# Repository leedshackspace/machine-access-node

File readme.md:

# Machine Node (WiFi)

Hardware and firmware to provide restricted access to dangerous and delicate
tools. Built around an ESP8266 (WeMos D1 mini) and RFID-RC522 breakout.

Designed to be easy to build for all levels of experience - simply order the PCB
from DirtyPCBs or OSHPark and solder the through hole parts to the board.
Software builds through the Arduino environment and will flash directly to the
WeMos board over USB.

## Hardware

To build a machine node you simply need to acquire a PCB - gerbers are available
in the hardware folder - and order the parts listed in the BOM.

[Schematic](hardware/images/schematic-rev1.png).

### Power Supply Options

There are three power supply options.

* **12 V DC Power**  
  This is the recommended option. Populate the 12 V DC section of the schematic, and also `C4` if you wish.
* **5 V DC Power** (Untested)  
  Populate the 12 V DC section of the schematic, and do not fit `U2` or `D2`. Use a jumper wire to bridge `D2` and connect the solder jumper `JP1`.  
  There is no polarity protection in this configuration.
* **240 AC Mains Power** (Untested)  
  Populate the 240 V AC section of the schematic. There is a PTC fuse inside the AC-DC power supply `U3` but there should be external fusing as well to protect small gauge cabling coming into the terminals.

### Relay Contacts

The relay is rated for 250 V, 6 A max. If you are switching heavy loads it is recommended that you use this to trip an external contactor.

### Latch Mode

The default state is "Present" mode, that is, the output will turn on when the card
is present and it will turn off when it is removed. An as yet untested mode allows the
node to read a card once and then keep the output enabled until an external signal is
received.

Feel free to test this mode out, you can modify settings in `settings.h`. Remember to include a button to allow the user to cancel their session.

### Faceplate

Enclosure parts are for laser cutting and will fit a [deep surface mount
pattress box](https://www.screwfix.com/p/lap-1-gang-surface-pattress-box-w-cable-clamp-earth-terminal-white-46mm/28489) available from LAP. You need to countersink the "solid" back plate
and fit screws through into the backbox compartment to secure the PCB in place.
Nylon screws & nuts are recommended to secure the PCB to minimize any interference
with the RFID signal. Typical metal faceplate screws are acceptable to attach
the faceplate to the backbox.

## Software

### Library Requirements
* [MFRC522 RFID](https://github.com/miguelbalboa/rfid)
* [ArduinoJson](https://arduinojson.org/)
* [ESP8266RestClient](https://github.com/fabianofranca/ESP8266RestClient)

Modify `settings-example.h` and rename as `settings.h`.

Requires the [Tool API server](https://github.com/leedshackspace/tool-api) running somewhere accessible, at least until the cards have been cached.

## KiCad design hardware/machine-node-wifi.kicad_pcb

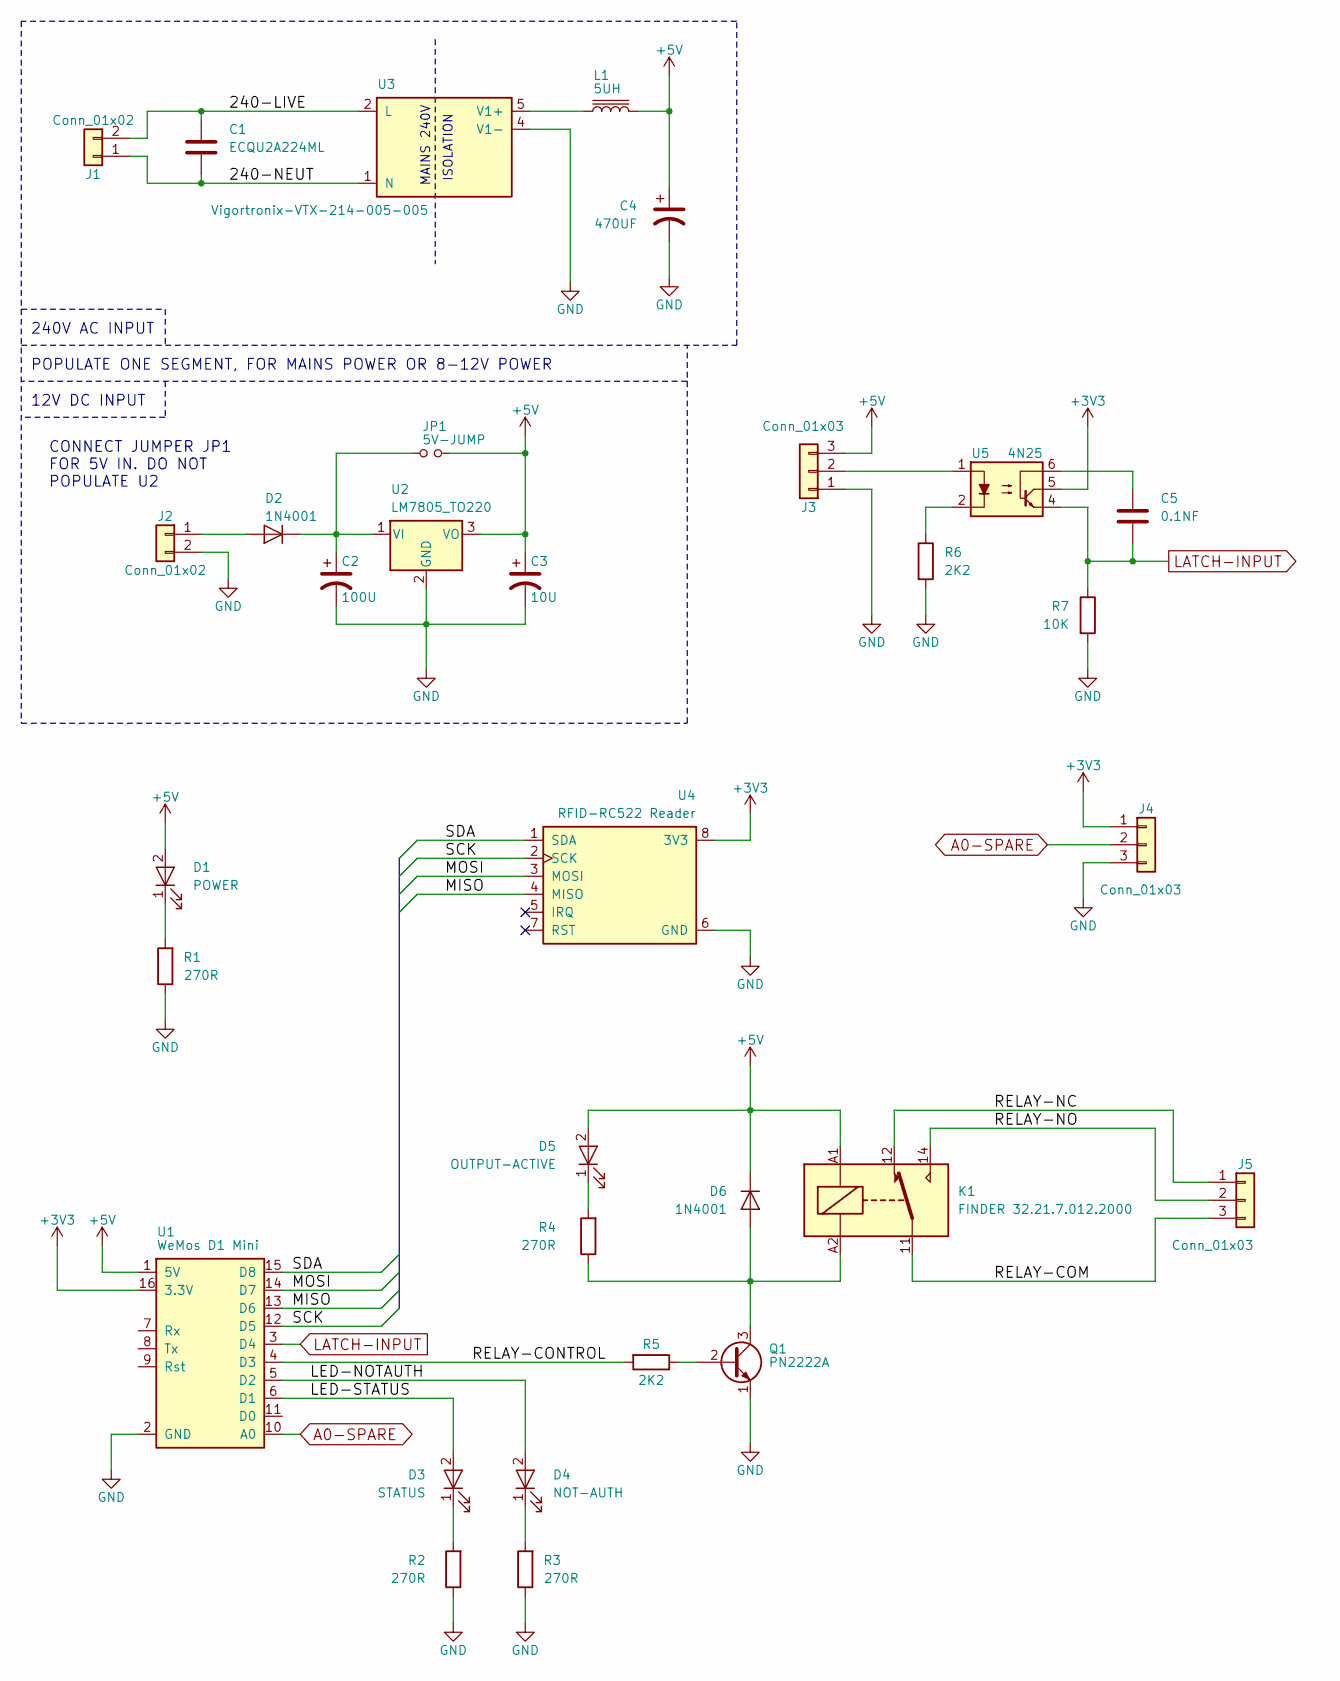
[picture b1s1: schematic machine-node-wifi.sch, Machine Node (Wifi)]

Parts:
C1: ECQU2A224ML; C_Rect_L18.0mm_W8.0mm_P15.00mm_FKS3_FKP3
C2: 100U; CP_Radial_D8.0mm_P3.50mm
C3: 10U; CP_Radial_D5.0mm_P2.00mm
C4: 470UF; CP_Radial_D8.0mm_P3.50mm
C5: 0.1NF; C_Rect_L4.0mm_W2.5mm_P2.50mm
D1: POWER; LED_D3.0mm
D2, D6: 1N4001; D_DO-41_SOD81_P10.16mm_Horizontal
D3: STATUS; LED_D3.0mm
D4: NOT-AUTH; LED_D3.0mm
D5: OUTPUT-ACTIVE; LED_D3.0mm
J1, J2: Conn_01x02; CONNECTOR-02-3.5MM
J3, J4, J5: Conn_01x03; CONNECTOR-03-3.5MM
JP1: 5V-JUMP; SOLDER-JUMPER_1-WAY
K1: FINDER 32.21.7.012.2000; Relay_SPDT_Finder_32.21-x000
L1: 5UH; INDUCTOR_V
Q1: PN2222A; TO-92_Molded_Narrow
R1, R2, R3, R4: 270R; R_Axial_DIN0207_L6.3mm_D2.5mm_P10.16mm_Horizontal
R5, R6: 2K2; R_Axial_DIN0207_L6.3mm_D2.5mm_P10.16mm_Horizontal
R7: 10K; R_Axial_DIN0207_L6.3mm_D2.5mm_P10.16mm_Horizontal
U1: WeMos D1 Mini; D1_mini_board
U2: LM7805_TO220; TO-220-3_Vertical
U3: Vigortronix-VTX-214-005-005; VTX-214-005-005
U4: RFID-RC522 Reader; Socket_Strip_Angled_1x08_Pitch2.54mm
U5: 4N25; DIP-6_W7.62mm

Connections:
+3V3: J4.1, U1.16 (3.3V), U4.8 (3V3), U5.5
+5V: C3.1, C4.1, D1.2 (A), D5.2 (A), D6.1 (K), J3.3, JP1.2, K1.A1, L1.1, U1.1 (5V), U2.3 (VO)
/240-LIVE: C1.1, J1.2, U3.2 (L)
/240-NEUT: C1.2, J1.1, U3.1 (N)
/LED-NOTAUTH: D4.2 (A), U1.5 (D2)
/LED-STATUS: D3.2 (A), U1.6 (D1)
/MISO: U1.13 (D6), U4.4 (MISO)
/MOSI: U1.14 (D7), U4.3 (MOSI)
/RELAY-COM: J5.3, K1.11
/RELAY-CONTROL: R5.2, U1.4 (D3)
/RELAY-NC: J5.1, K1.12
/RELAY-NO: J5.2, K1.14
/SCK: U1.12 (D5), U4.2 (SCK)
/SDA: U1.15 (D8), U4.1 (SDA)
A0-SPARE: J4.2, U1.10 (A0)
GND: C2.2, C3.2, C4.2, J2.2, J3.1, J4.3, Q1.1 (E), R1.1, R2.1, R3.1, R6.2, R7.2, U1.2 (GND), U2.2 (GND), U3.4 (V1-), U4.6 (GND)
LATCH-INPUT: C5.2, R7.1, U1.3 (D4), U5.4
unnamed: C2.1, D2.1 (K), JP1.1, U2.1 (VI)
unnamed: C5.1, U5.6
unnamed: D1.1 (K), R1.2
unnamed: D2.2 (A), J2.1
unnamed: D3.1 (K), R2.2
unnamed: D4.1 (K), R3.2
unnamed: D5.1 (K), R4.2
unnamed: D6.2 (A), K1.A2, Q1.3 (C), R4.1
unnamed: J3.2, U5.1
unnamed: L1.2, U3.5 (V1+)
unnamed: Q1.2 (B), R5.1
unnamed: R6.1, U5.2

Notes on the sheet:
POPULATE ONE SEGMENT, FOR MAINS POWER OR 8-12V POWER
240V AC INPUT
12V DC INPUT
MAINS 240V
ISOLATION
CONNECT JUMPER JP1 FOR 5V IN. DO NOT POPULATE U2

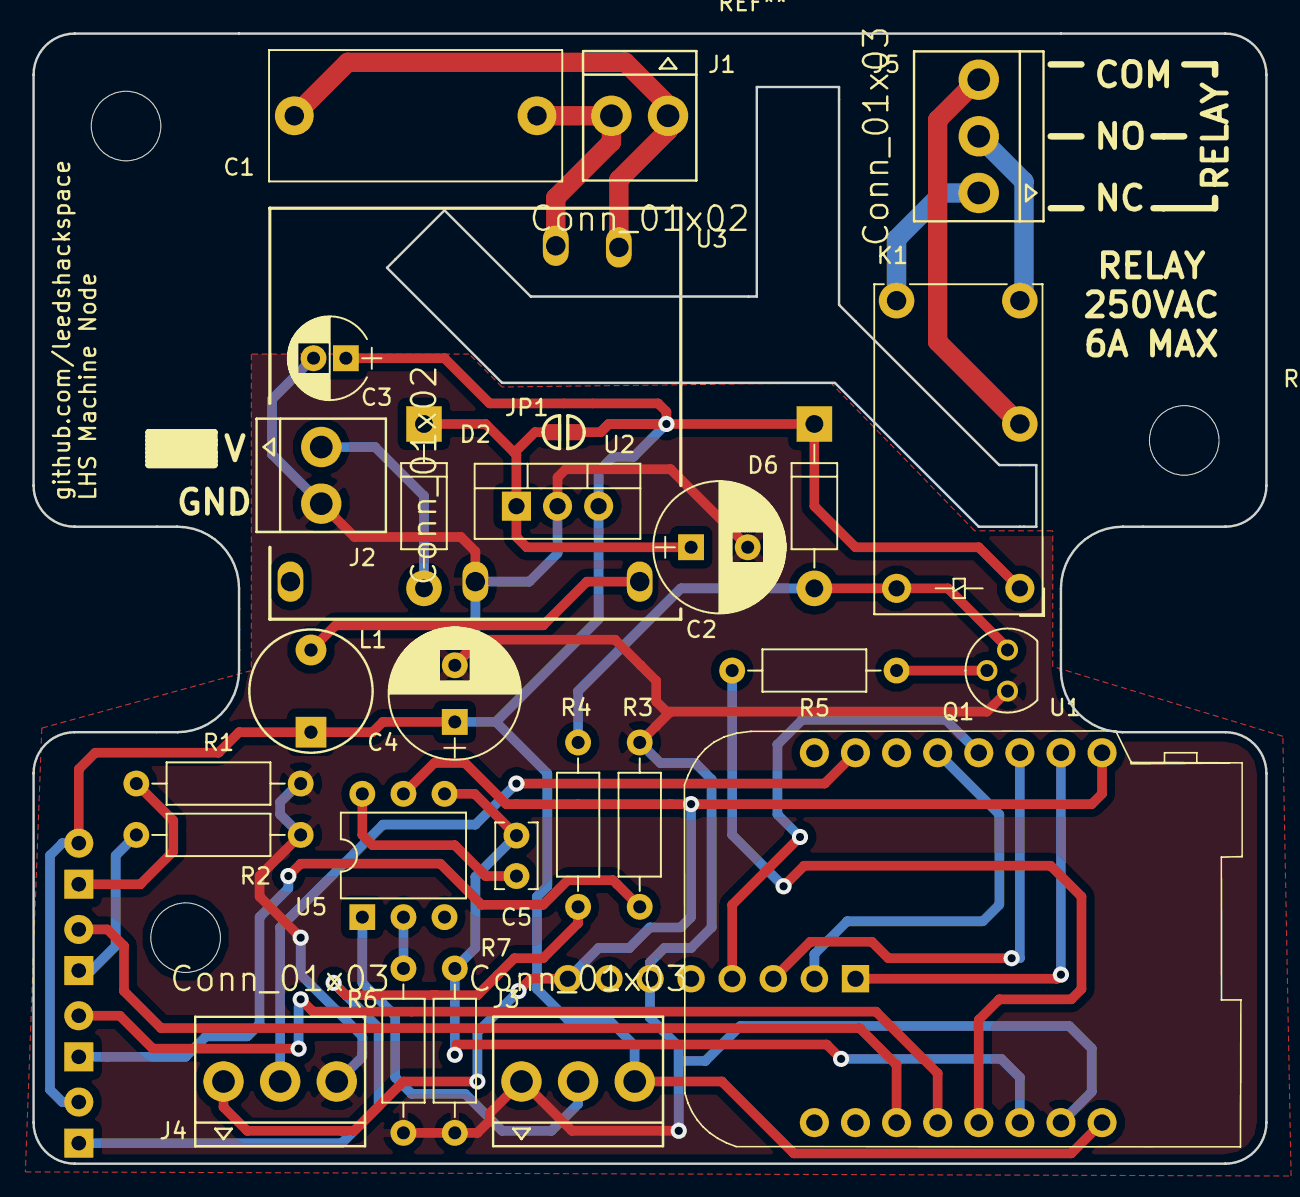
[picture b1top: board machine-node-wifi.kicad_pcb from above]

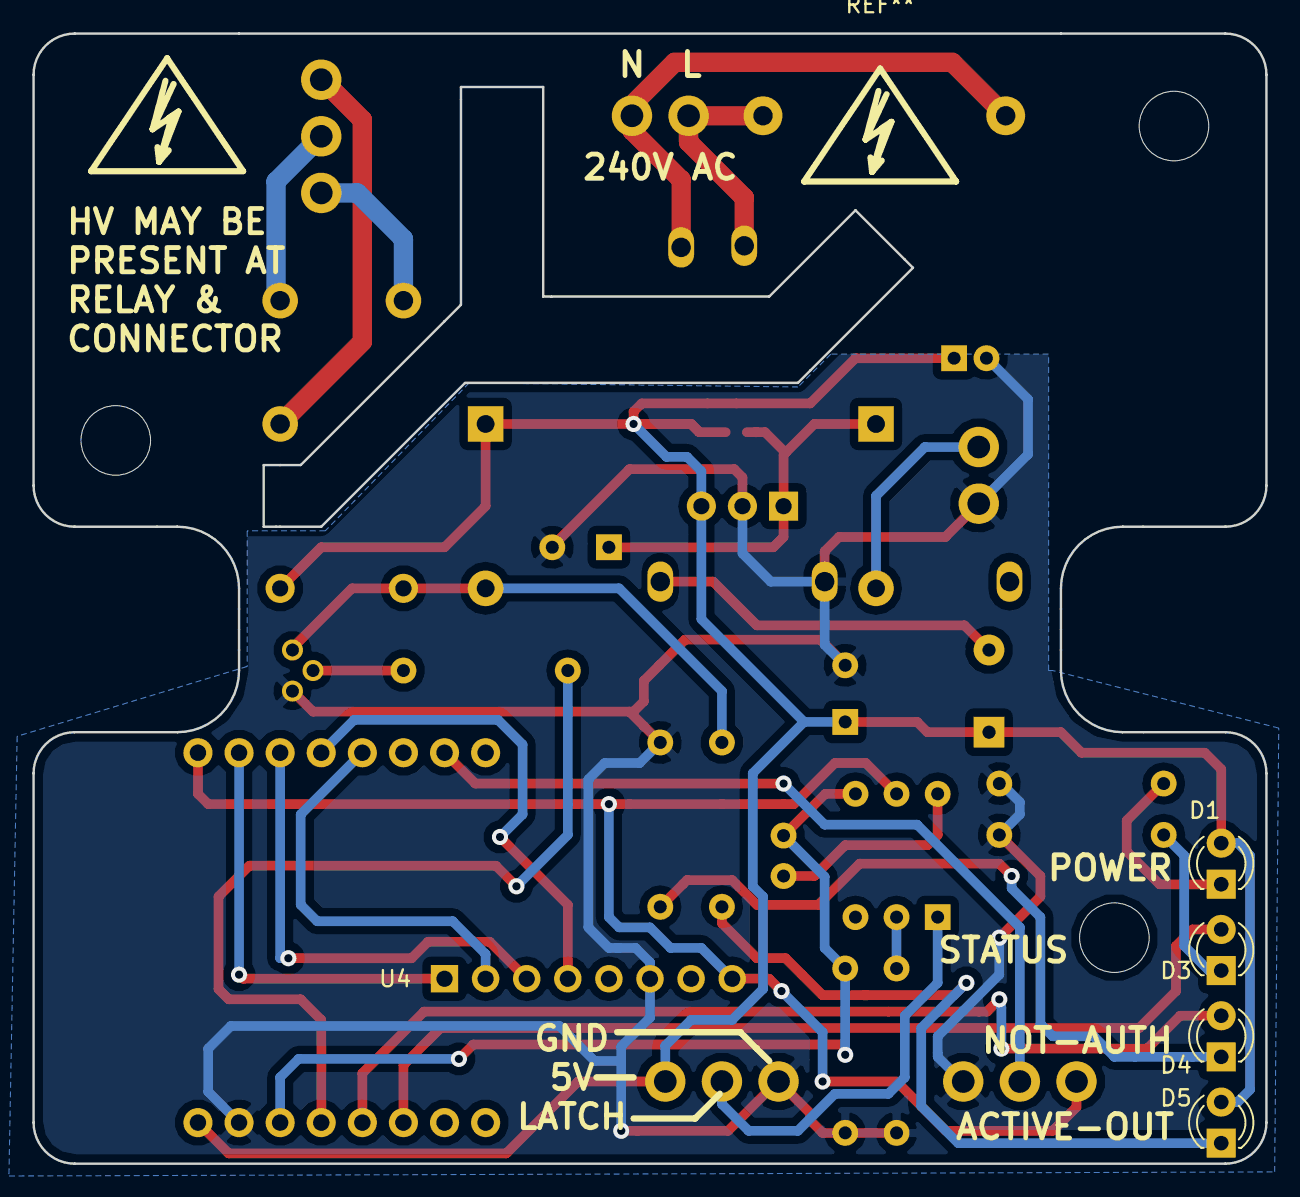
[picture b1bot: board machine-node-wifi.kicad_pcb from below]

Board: 2 copper layers, 76.2 x 69.9 mm, 32 parts (5 on the bottom side), 29 nets.

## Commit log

2018-02-18 First commit - ESP Code
    Inc. gitignore updates.
2018-02-18 First commit - KiCad & Gerbers
    KiCad schematic and layout files, gerbers.
2018-02-18 First commit - Enclosure hardware
2018-02-18 First commit - Readme & images
2018-02-19 No wifi, don't check server
    If the WiFi isn't connected then don't bother trying to talk to the
    server - speeds up the response and prevents spurious ESP exceptions.
2018-03-11 Start log timer after card has been checked
